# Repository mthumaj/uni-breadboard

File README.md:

# Universal Breadboard (uni-breadboard)

Breadboard based on 4mm banana plugs designed for easier connection of device with test environment while developing/debugging/testing.

**Features:**
* 24 banana plugs (4mm) screwed-in on custom PCB (10 x 10cm)
* Switch and button to power on/off - for easy power reset of device
* LIN Bus input (LIN_IN) with selection option to connect to LIN_1 or/and LIN_2 channel
* 2 D-SUB9 LIN/CAN interfaces
* 5 General purpose ports (A-E)
* D-SUB9 connector dedicated as port interface (optimized for Vector VN1640 Digital/Analog IO interface (CH5))

## Detailed Description

Breadboard is composed from PCB and 3D printed case/box. 
Plugs/connectors from case are connected to the PCB by wires and screw terminals. 

### Front Panel

**Banana plugs**

| Number 	| Signal 	|
| :---: 	| :---: 	|
| 1 		| GND 		|
| 2 		| V_OUT 	|
| 3 		| LIN_IN 	|
| 4 		| PORT_A 	|
| 5 		| PORT_B 	|
| 6 		| PORT_C 	|
| 7 		| PORT_D 	|
| 8 		| PORT_E 	|

*Note: Numbering starts from left

### Switches (from left)

**Power switch**
* Top position: 	Power OFF
* Bottom position:	Power ON (V_IN --> V_OUT)
	
**Power reset button** - only if Power switch is in bottom position (Power is ON)
* Released:			Power ON
* Pressed:			Power OFF
	
**LIN selector switch**
* Left position: 	LIN_IN --> LIN_1
* Middle position:	LIN_IN - not connected
* Right position:	LIN_IN --> LIN_2
	
**LIN_1 and LIN_2 connection switch**
* Top position: 	LIN_1 and LIN_2 not connected
* Bottom position:	LIN_1 and LIN_2 connected

### Back Panel

**Banana plugs**
| Number 	| Signal 	|
| :---: 	| :---: 	|
| 1 		| V_IN 		|
| 2 		| GND 		|

*Note: Numbering starts from left

**Right D-SUB9 Connector - LIN/CAN Interface 1**

| Number 	| Signal 			|
| :---: 	| :---: 			|
| 2 		| CAN_L_1 			|
| 3 		| GND 				|
| 7			| LIN_1/CAN_H_1		|

Others are not connected

**Left D-SUB9 Connector - LIN/CAN Interface 2**

| Number 	| Signal 			|
| :---: 	| :---: 			|
| 2 		| CAN_L_2 			|
| 3 		| GND 				|
| 7			| LIN_1/CAN_H_2		|

Others are not connected

### Right Panel

**D-SUB9 Connector - Analog/Digital Interface**

| Number 	| Signal 	|
| :---: 	| :---: 	|
| 1 		| A_IN 		|
| 2 		| NC 		|
| 3 		| NC 		|
| 4 		| D_IN_1 	|
| 5 		| D_IN_2 	|
| 6 		| A_GND 	|
| 7 		| NC	 	|
| 8 		| D_OUT 	|
| 9			| D_GND		|

*Refer to: https://cdn.vector.com/cms/content/products/VN16xx/docs/VN1600_Interface_Family_Manual_EN.pdf chapter 2.6.8*

Ports connection (PORT_A - PORT_E) to Analog/Digital Interface can be established by jumpers/wires on J7 

## Build Manual/Notes

1. 3D Print breadboard case from [here](/02_Mechanical_Design/BreadboardBox_1.STL)
	* No supports needed
	* 0.6mm nozzle can be used to speed up printing
2. Insert and glue M3 hex nuts.
3. Assembly the PCB 
	* gerber files to manufacture are available [here](/01_PCB/Breadboard/gerbers)
	* BOM is available [here](BOM.xlsx)
	* When assembling screw terminals, make sure that wire openings are oriented inside the board (see picture), so wires can be easily inserted to the terminal, when board is already mounted on top of case.
4. Solder cables for banana plugs, switches and D-SUB9 connectors
	* For V_IN, V_OUT and GND connection use cable with cross section at least 1,5mm^2
5. Mount banana plugs/switches/D-SUB9 connectors to the case
	* When mounting banana plugs, use serrated lock washers (washer with "teeth") to prevent releasing when plug and unplug connectors to the plugs.
6. Connect wires to the respected screw terminals
7. ...and it's done.

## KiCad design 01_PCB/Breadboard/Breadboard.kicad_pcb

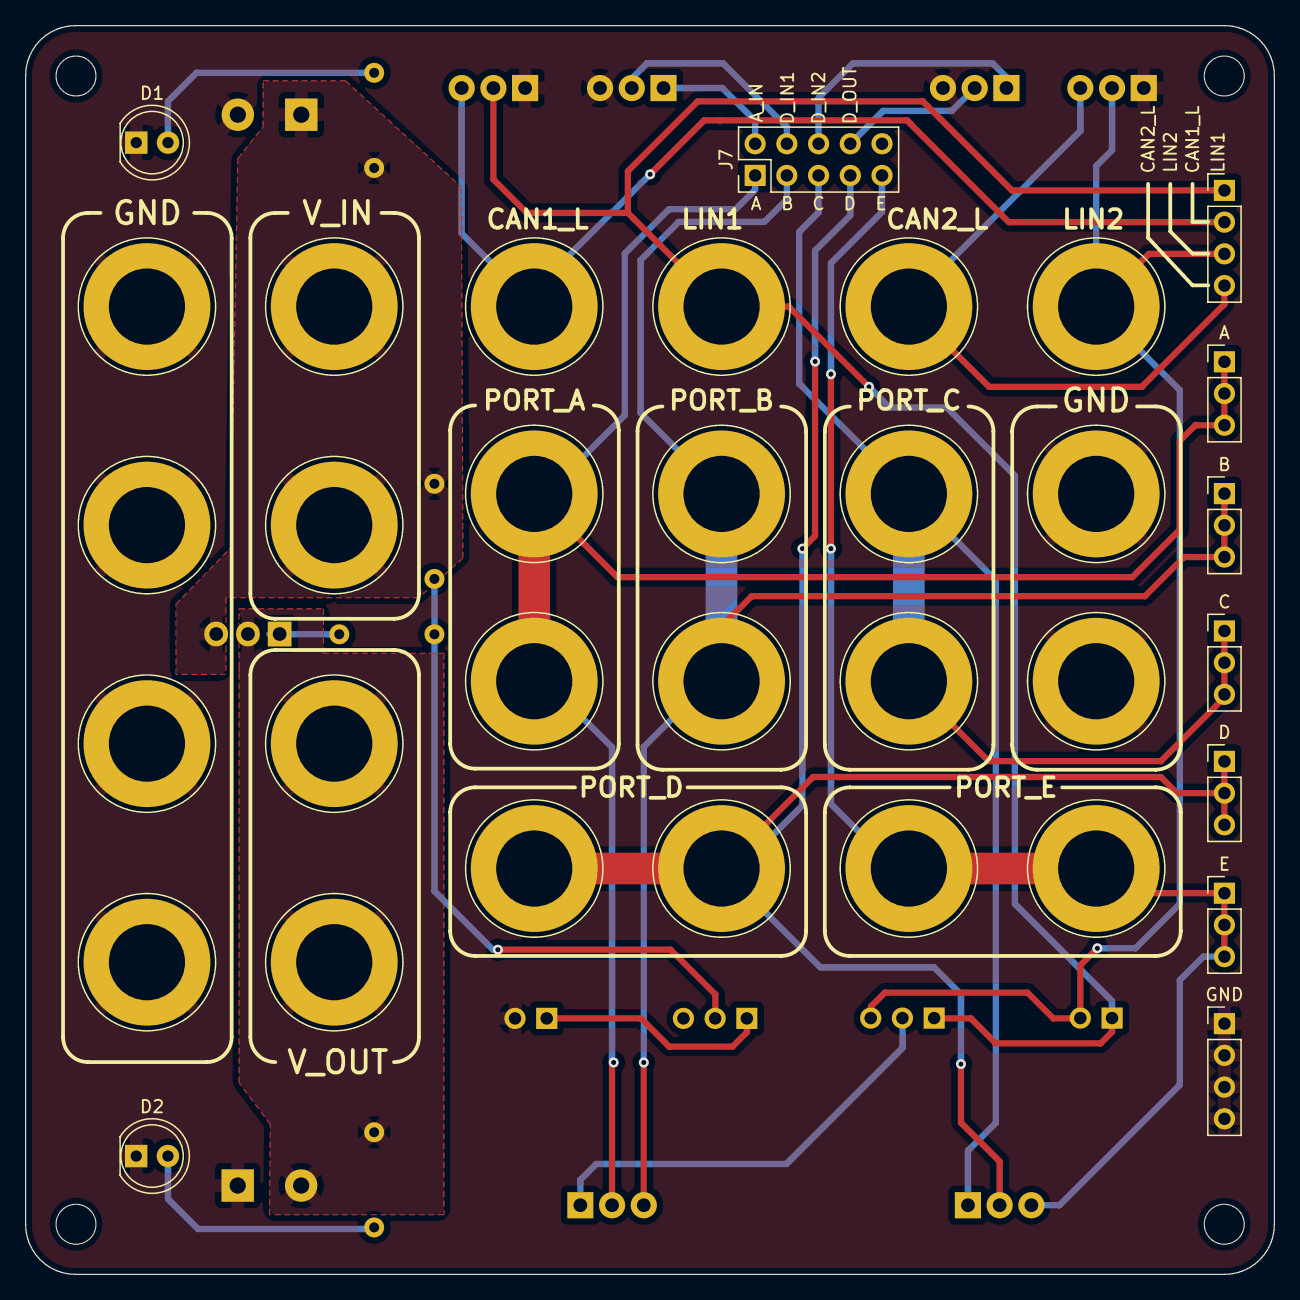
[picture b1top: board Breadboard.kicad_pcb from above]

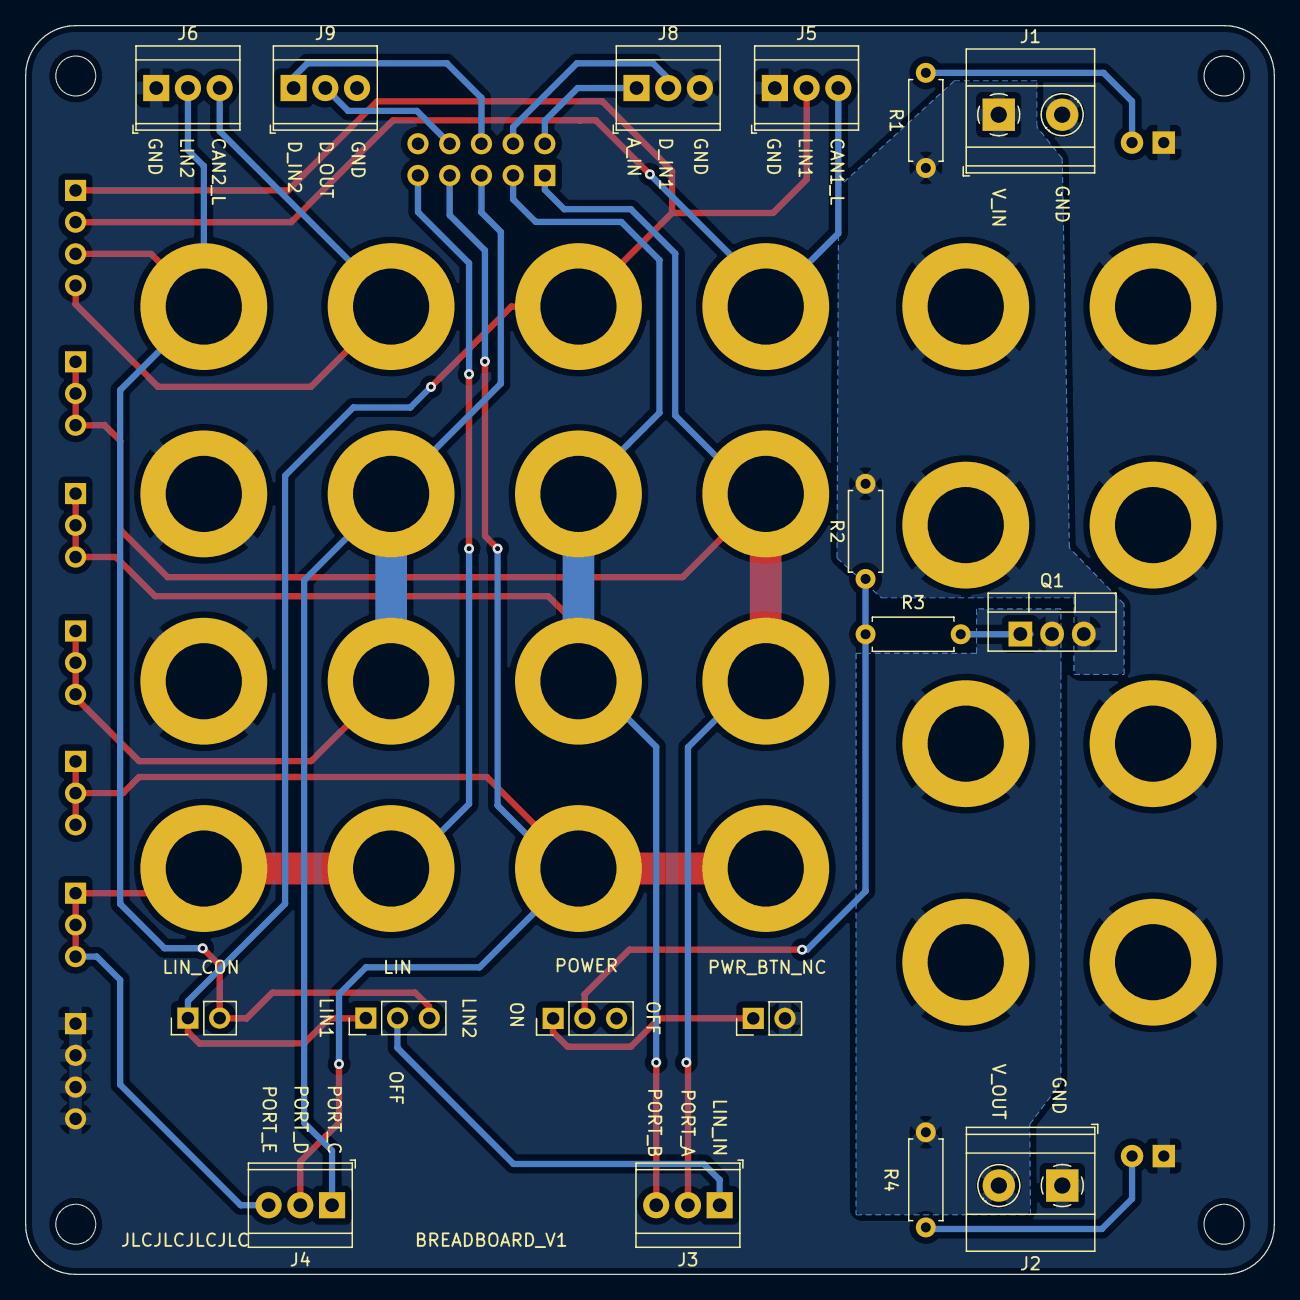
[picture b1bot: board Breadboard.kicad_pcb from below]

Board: 2 copper layers, 100.0 x 100.0 mm, 26 parts (17 on the bottom side), 20 nets.

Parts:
A: PinHeader_1x03_P2.54mm_Vertical
B: PinHeader_1x03_P2.54mm_Vertical
C: PinHeader_1x03_P2.54mm_Vertical
D: PinHeader_1x03_P2.54mm_Vertical
D1: V_IN; LED_D5.0mm
D2: V_OUT; LED_D5.0mm
E: PinHeader_1x03_P2.54mm_Vertical
GND: PinHeader_1x04_P2.54mm_Vertical
J1, J2: Screw_Terminal_01x02; TerminalBlock_Phoenix_MKDS-1,5-2-5.08_1x02_P5.08mm_Horizont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
J3, J4, J5, J6, J8, J9: Screw_Terminal_01x03; TerminalBlock_TE_282834-3_1x03_P2.54mm_Horizontal
J7: Conn_02x05_Odd_Even; PinHeader_2x05_P2.54mm_Vertical
LIN: SW_SPDT_MSM; PinHeader_1x03_P2.54mm_Vertical
LIN_CON: SW_SPST; PinHeader_1x02_P2.54mm_Vertical
POWER: SW_SPDT; PinHeader_1x03_P2.54mm_Vertical
PWR_BTN_NC: SW_Push_Open; PinHeader_1x02_P2.54mm_Vertical
Q1: IRF4905; TO-220-3_Vertical
R1, R4: 560R; R_Axial_DIN0207_L6.3mm_D2.5mm_P7.62mm_Horizontal
R2: 10K; R_Axial_DIN0207_L6.3mm_D2.5mm_P7.62mm_Horizontal
R3: 100R; R_Axial_DIN0207_L6.3mm_D2.5mm_P7.62mm_Horizontal

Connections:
/A_IN: J7.2, J8.1
/D_IN_1: J7.4, J8.2
/D_IN_2: J7.6, J9.1
/D_OUT: J7.8, J9.2
/PORT_A: A.1, A.2, A.3, J3.2, J7.1
/PORT_B: B.1, B.2, B.3, J3.3, J7.3
/PORT_C: C.1, C.2, C.3, J4.1, J7.5
/PORT_D: D.1, D.2, D.3, J4.2, J7.7
/PORT_E: E.1, E.2, E.3, J4.3, J7.9
CAN_H_1: J5.2, LIN.1, LIN_CON.1 (A)
CAN_H_2: J6.2, LIN.3, LIN_CON.2 (B)
GND: D1.1 (K), D2.1 (K), GND.1, GND.2, GND.3, GND.4, J1.2, J2.1, J5.1, J6.1, J8.3, J9.3, PWR_BTN_NC.2 (B)
LIN_IN: J3.1, LIN.2
unnamed: D1.2 (A), R1.2
unnamed: D2.2 (A), R4.2
unnamed: Q1.1 (G), R3.1
unnamed: POWER.2 (B), R2.2, R3.2
unnamed: POWER.1 (A), PWR_BTN_NC.1 (A)
VIN: J1.1, Q1.3 (S), R1.1, R2.1
VOUT: J2.2, Q1.2 (D), R4.1

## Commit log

2022-03-31 Update PCB
2022-03-31 Update mechanical parts
2022-04-02 Update LICENSE
    Change from software to product
2022-04-02 Add README.md, Add renders
2022-04-02 Fix top silkscreen
    Generate new gerbers.
2022-04-02 Upload BOM
2022-04-02 Fix link to .STL file
